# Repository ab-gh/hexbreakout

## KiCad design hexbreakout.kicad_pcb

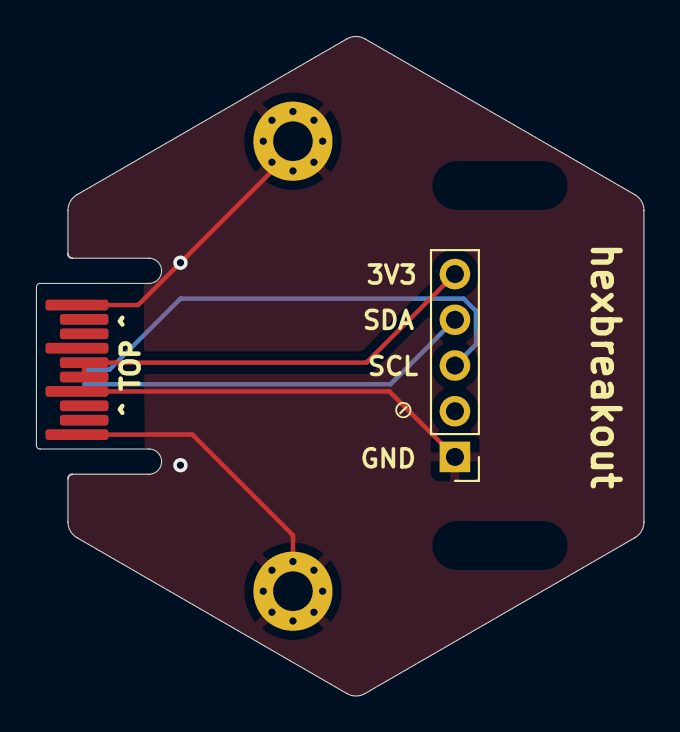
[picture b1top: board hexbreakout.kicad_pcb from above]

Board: 2 copper layers, 33.7 x 36.6 mm, 3 parts (0 on the bottom side), 2 nets.

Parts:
H1, H2: MountingHole_Pad; MountingHole_2.2mm_M2_Pad_Via
J1: Nodule-Connector; hexpansion-edge-connector

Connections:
/3V3: J1.15 (3V3), J1.16 (3V3)
/GND: H1.1, H2.1, J1.1 (GND), J1.10 (GND), J1.11 (GND), J1.14 (GND), J1.17 (GND), J1.20 (GND)

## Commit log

2024-03-18 rev0
